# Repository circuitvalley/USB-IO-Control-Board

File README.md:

USB-IO-Control-Board
=================
/* 
 * File:   main.c
 * Author: Gaurav Chaudhary
 * email : mailchaduarygaurav@gmail.com
 * copy right : www.circuitvalley.com 
 * http://www.circuitvalley.com/2011/09/pic-18f4550-usb-io-input-output-board.html
 * http://www.circuitvalley.com/2015/10/usb-io-board-linux-mac-osx-windows-cross-platform-pwm-analog-qt5-qt-creator.html
 */

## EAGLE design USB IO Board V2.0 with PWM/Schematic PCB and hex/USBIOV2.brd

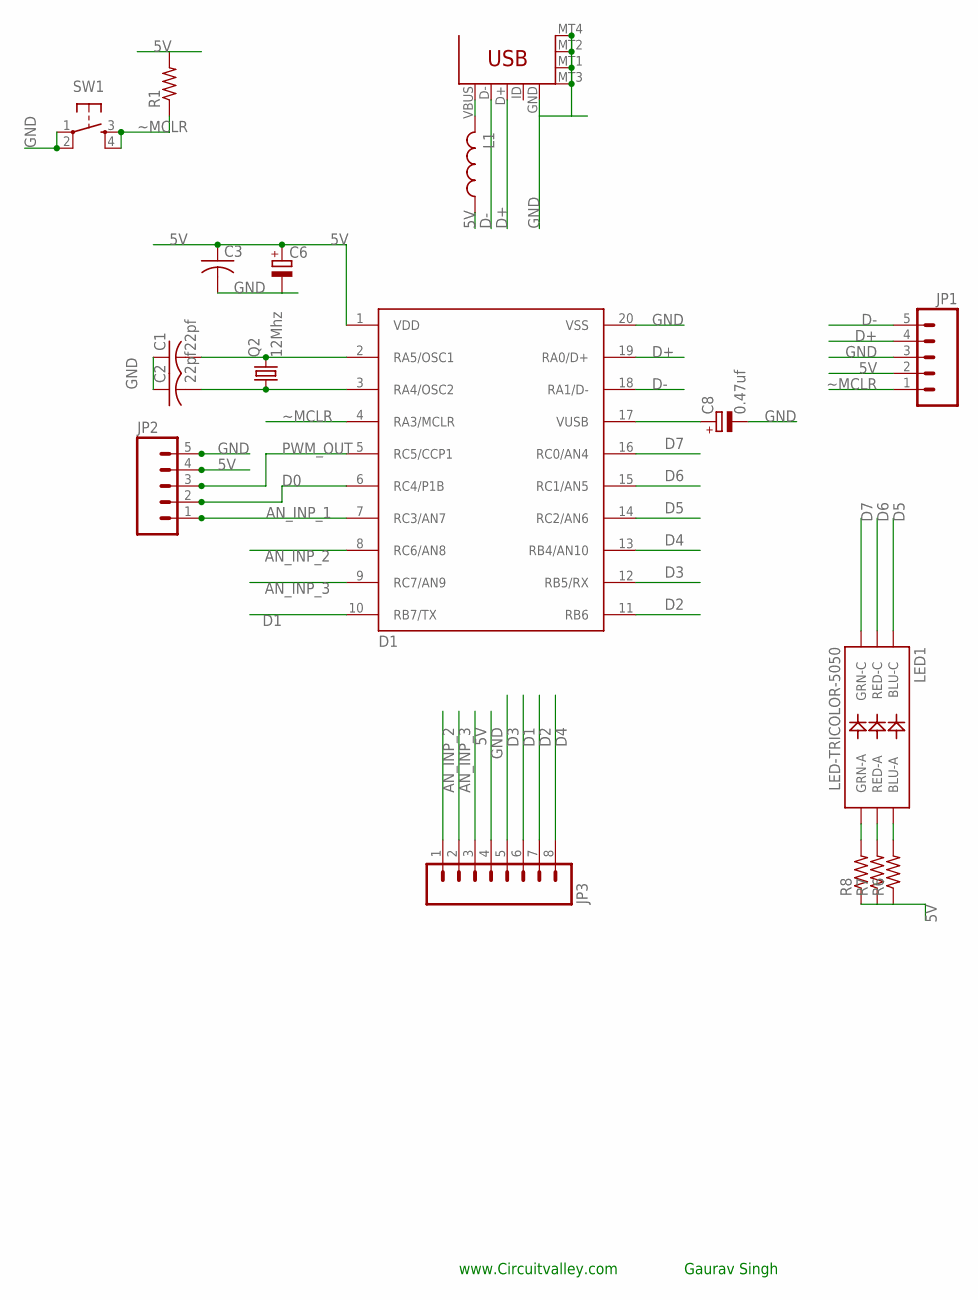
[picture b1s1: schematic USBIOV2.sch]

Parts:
C1, C2: 22pf; C0805
C3: C-USC0805; C0805
C6: CAP_POLSMC_B; SMC_B
C8: 0.47uf; SMC_B
D1: PIC18F14K50D; SSOP20
JP1, JP2: M05PTH; 1X05
JP3: M081X08; 1X08
L1: L-USL3225M; L3225M
LED1: LED-TRICOLOR-5050
Q2: 12Mhz; HC49UP
R1, R6, R7, R8: R-US_M0805; M0805
SW1: SW-SMD-SMALL; TACT_SWITCH_SMALL
U$1: USB-MICROB-HW-MC-5F; USB-MICROB-HW-MC-5F-01

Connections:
5V: C3.1, C6.+, D1.1 (VDD), JP1.2, JP2.4, JP3.3, L1.1, R1.2, R6.1, R7.1, R8.1
AN_INP_1: D1.7 (RC3/AN7), JP2.1
AN_INP_2: D1.8 (RC6/AN8), JP3.1
AN_INP_3: D1.9 (RC7/AN9), JP3.2
D0: D1.6 (RC4/P1B), JP2.2
D1: D1.10 (RB7/TX), JP3.6
D2: D1.11 (RB6), JP3.7
D3: D1.12 (RB5/RX), JP3.5
D4: D1.13 (RB4/AN10), JP3.8
D5: D1.14 (RC2/AN6), LED1.1 (BLU-C)
D6: D1.15 (RC1/AN5), LED1.2 (RED-C)
D7: D1.16 (RC0/AN4), LED1.3 (GRN-C)
D+: D1.19 (RA0/D+), JP1.4, U$1.D+
D-: D1.18 (RA1/D-), JP1.5, U$1.D-
GND: C1.1, C2.1, C3.2, C6.-, C8.-, D1.20 (VSS), JP1.3, JP2.5, JP3.4, SW1.1, SW1.2, U$1.GND, U$1.MT1 (MTN3), U$1.MT2 (MTN4), U$1.MT3 (MTN1), U$1.MT4 (MTN2)
unnamed: C2.2, D1.3 (RA4/OSC2), Q2.1
unnamed: C1.2, D1.2 (RA5/OSC1), Q2.2
unnamed: LED1.6 (BLU-A), R6.2
unnamed: LED1.5 (RED-A), R7.2
unnamed: LED1.4 (GRN-A), R8.2
unnamed: C8.+, D1.17 (VUSB)
PWM_OUT: D1.5 (RC5/CCP1), JP2.3
VBUS5V: L1.2, U$1.VBUS
~MCLR: D1.4 (RA3/MCLR), JP1.1, R1.1, SW1.3, SW1.4

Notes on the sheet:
www.Circuitvalley.com
Gaurav Singh

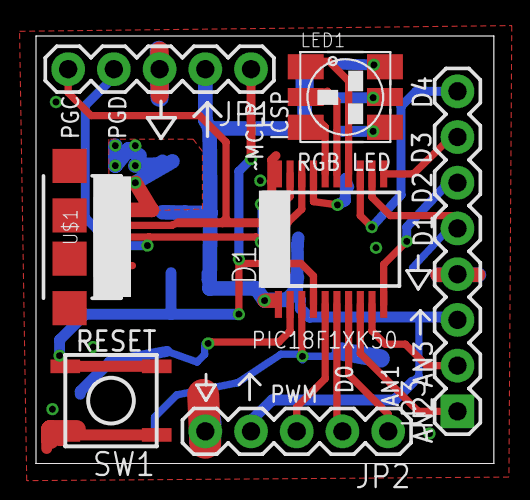
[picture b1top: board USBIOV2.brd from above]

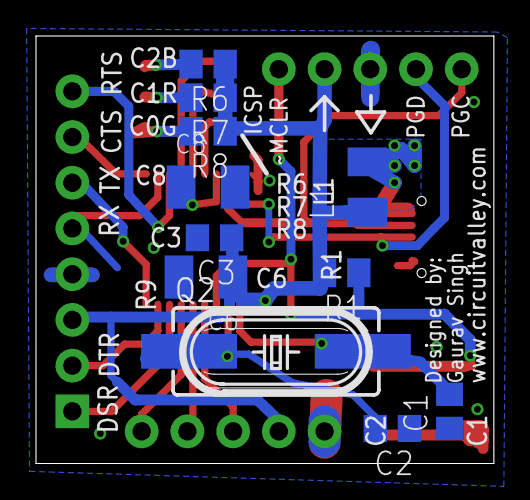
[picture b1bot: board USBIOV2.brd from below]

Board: 2 copper layers, 25.4 x 23.8 mm, 18 parts (11 on the bottom side), 24 nets.

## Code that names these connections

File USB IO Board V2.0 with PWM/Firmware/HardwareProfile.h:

/********************************************************************
 FileName:     main.c
 Dependencies:   See INCLUDES section
 Processor:		PIC18, PIC24, and PIC32 USB Microcontrollers
 Hardware:		www.circuitvalley.com USB IO board V2
 Complier:  	Microchip C18 (for PIC18)
 Company:		www.circuitvalley.com

 Software License Agreement:
 THIS SOFTWARE IS PROVIDED IN AN AS IS CONDITION. NO WARRANTIES,
 WHETHER EXPRESS, IMPLIED OR STATUTORY, INCLUDING, BUT NOT LIMITED
 TO, IMPLIED WARRANTIES OF MERCHANTABILITY AND FITNESS FOR A
 PARTICULAR PURPOSE APPLY TO THIS SOFTWARE. THE COMPANY SHALL NOT,
 IN ANY CIRCUMSTANCES, BE LIABLE FOR SPECIAL, INCIDENTAL OR
 CONSEQUENTIAL DAMAGES, FOR ANY REASON WHATSOEVER.
*/

#ifndef _HW_PROFILE_H_
#define _HW_PROFILE_H_

    /*******************************************************************/
    /******** USB stack hardware selection options *********************/
    /*******************************************************************/
    //This section is the set of definitions required by the MCHPFSUSB
    //  framework.  These definitions tell the firmware what mode it is
    //  running in, and where it can find the results to some information
    //  that the stack needs.
    //These definitions are required by every application developed with
    //  this revision of the MCHPFSUSB framework.  Please review each
    //  option carefully and determine which options are desired/required
    //  for your application.

    //#define USE_SELF_POWER_SENSE_IO	
    #define tris_self_power     TRISAbits.TRISA2    // Input
    #if defined(USE_SELF_POWER_SENSE_IO)
    #define self_power          PORTAbits.RA2
    #else
    #define self_power          1
    #endif

    //#define USE_USB_BUS_SENSE_IO
    #define tris_usb_bus_sense  TRISAbits.TRISA1    // Input
    #if defined(USE_USB_BUS_SENSE_IO)
    #define USB_BUS_SENSE       PORTAbits.RA1
    #else
    #define USB_BUS_SENSE       1
    #endif


    //Uncomment the following line to make the output HEX of this 
    //  project work with the HID Bootloader
    #define PROGRAMMABLE_WITH_USB_HID_BOOTLOADER	

    /** Board definition ***********************************************/
    //These defintions will tell the main() function which board is
    //  currently selected.  This will allow the application to add
    //  the correct configuration bits as wells use the correct
    //  initialization functions for the board.  These defitions are only
    //  required in the stack provided demos.  They are not required in
    //  final application design.
    
    #define CLOCK_FREQ 48000000
    
    /** LED ************************************************************/
    #define mInitAllIO()      LATC = 0x00; TRISC = 0xDF; LATB &=0x00; TRISB = 0xFF;	//TRISC5 for PWM
    
  

	#define DIO0	PORTCbits.RC4
	#define DIO1	PORTBbits.RB7
	#define DIO2	PORTBbits.RB6
	#define DIO3	PORTBbits.RB5
	#define DIO4	PORTBbits.RB4
	#define DIO5	PORTCbits.RC2
	#define DIO6	PORTCbits.RC1
	#define DIO7	PORTCbits.RC0

	#define DIO0_LAT	LATCbits.LATC4
	#define DIO1_LAT	LATBbits.LATB7
	#define DIO2_LAT	LATBbits.LATB6
	#define DIO3_LAT	LATBbits.LATB5
	#define DIO4_LAT	LATBbits.LATB4
	#define DIO5_LAT	LATCbits.LATC2
	#define DIO6_LAT	LATCbits.LATC1
	#define DIO7_LAT	LATCbits.LATC0


	#define DIO0_TRIS	TRISCbits.TRISC4
	#define DIO1_TRIS	TRISBbits.TRISB7
	#define DIO2_TRIS	TRISBbits.TRISB6
	#define DIO3_TRIS	TRISBbits.TRISB5
	#define DIO4_TRIS	TRISBbits.TRISB4
	#define DIO5_TRIS	TRISCbits.TRISC2
	#define DIO6_TRIS	TRISCbits.TRISC1
	#define DIO7_TRIS	TRISCbits.TRISC0
    #define ANALOG1_TRIS TRISCbits.TRISC3
    #define ANALOG2_TRIS TRISCbits.TRISC6
    #define ANALOG3_TRIS TRISCbits.TRISC7

    /** I/O pin definitions ********************************************/
    #define INPUT_PIN 1
    #define OUTPUT_PIN 0

#endif  //HARDWARE_PROFILE_LOW_PIN_COUNT_USB_DEVELOPMENT_KIT_H

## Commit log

2014-01-22 cleanup
2014-07-18 BUGFIX:Aanalog Read was Switching all I/O channel to digital fixed
2014-07-18 BUG FIX:Aanalog Read was Switching all I/O channel to inputs fixed
2015-10-03 USB I/O Board V2.0 with PWM firmware added
2015-10-04 qt application source and binary added
2015-10-04 windows dll file added
2015-10-04 more windows dll added
2015-10-04 added all of dll files

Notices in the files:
parts and their libraries:
SparkFun: Licensing: CC v3.0 Share-Alike You are welcome to use this library for commercial purposes.
